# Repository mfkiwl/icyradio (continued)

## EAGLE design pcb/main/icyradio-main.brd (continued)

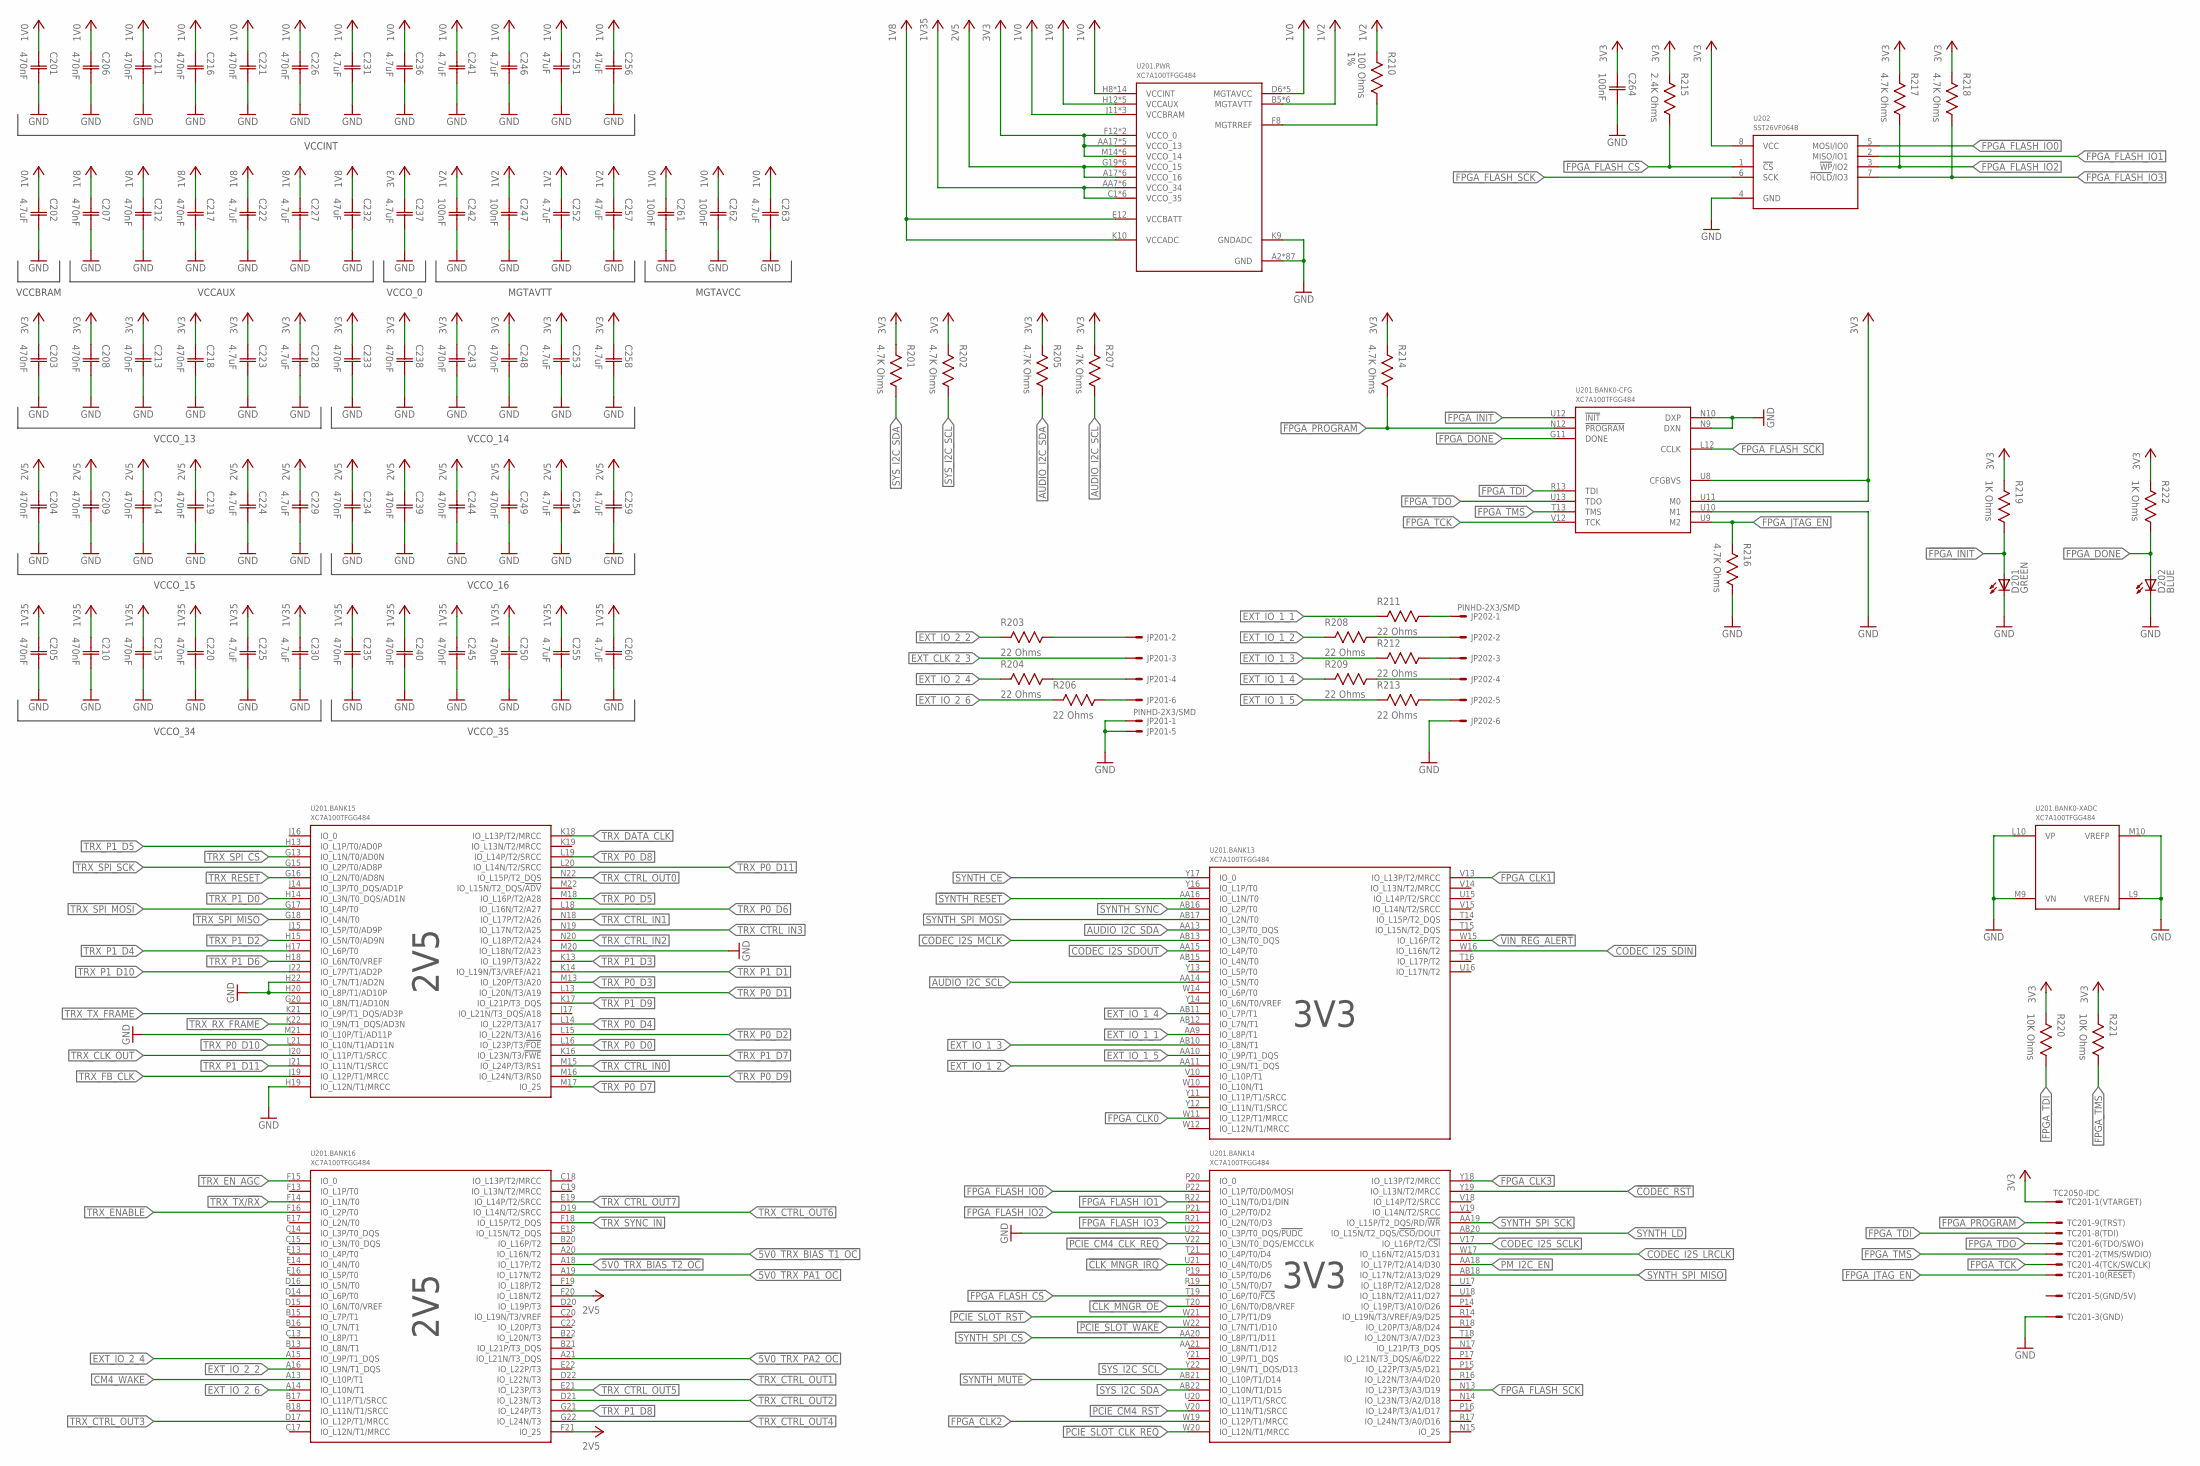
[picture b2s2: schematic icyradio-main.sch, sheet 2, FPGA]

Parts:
C201, C203, C204, C205, C206, C207, C208, C209, C210, C211, C212, C213, C214, C215, C216, C217, C218, C219, C220, C221, C226, C233, C234, C235, C238, C239, C240, C243, C244, C245, C248, C249, C250: 470nF; CAP0402
C202, C222, C223, C224, C225, C227, C228, C229, C230, C231, C236, C237, C241, C246, C252, C253, C254, C255, C258, C259, C260, C263: 4.7uF; CAP0402
C232, C251, C256, C257: 47uF; CAP0603
C242, C247, C261, C262, C264: 100nF; CAP0402
D201, D202: LED0603; 0603
JP201, JP202: PINHD-2X3/SMD; 2X03/SMD
R201, R202, R205, R207, R214, R216, R217, R218: 4.7K Ohms; RES0402
R203, R204, R206, R208, R209, R211, R212, R213: 22 Ohms; RES0402
R210: 100 Ohms; RES0402; TOLERANCE 1%
R215: 2.4K Ohms; RES0402
R219, R222: 1K Ohms; RES0402
R220, R221: 10K Ohms; RES0402
TC201: TC2050-IDC
U201: XC7A100TFGG484; FGG484
U202: SST26VF064B; WSOIC8

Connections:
1V0: C201.1 (C1), C202.1 (C1), C206.1 (C1), C211.1 (C1), C216.1 (C1), C221.1 (C1), C226.1 (C1), C231.1 (C1), C236.1 (C1), C241.1 (C1), C246.1 (C1), C251.1 (C1), C256.1 (C1), C261.1 (C1), C262.1 (C1), C263.1 (C1), U201.D6 (MGTAVCC), U201.D10 (MGTAVCC), U201.E8 (MGTAVCC), U201.F7 (MGTAVCC), U201.F9 (MGTAVCC), U201.H8 (VCCINT), U201.H10 (VCCINT), U201.J7 (VCCINT), U201.J9 (VCCINT), U201.J11 (VCCBRAM), U201.K8 (VCCINT), U201.L7 (VCCINT), U201.L11 (VCCBRAM), U201.M8 (VCCINT), U201.N7 (VCCINT), U201.N11 (VCCBRAM), U201.P8 (VCCINT), U201.P10 (VCCINT), U201.R7 (VCCINT), U201.R9 (VCCINT), U201.T8 (VCCINT), U201.T10 (VCCINT); also elsewhere on the board
1V2: C242.1 (C1), C247.1 (C1), C252.1 (C1), C257.1 (C1), R210.2, U201.B5 (MGTAVTT), U201.B7 (MGTAVTT), U201.B9 (MGTAVTT), U201.B11 (MGTAVTT), U201.C4 (MGTAVTT), U201.C8 (MGTAVTT); also elsewhere on the board
1V8: C207.1 (C1), C212.1 (C1), C217.1 (C1), C222.1 (C1), C227.1 (C1), C232.1 (C1), U201.E12 (VCCBATT), U201.H12 (VCCAUX), U201.K10 (VCCADC), U201.K12 (VCCAUX), U201.M12 (VCCAUX), U201.P12 (VCCAUX), U201.R11 (VCCAUX); also elsewhere on the board
1V35: C205.1 (C1), C210.1 (C1), C215.1 (C1), C220.1 (C1), C225.1 (C1), C230.1 (C1), C235.1 (C1), C240.1 (C1), C245.1 (C1), C250.1 (C1), C255.1 (C1), C260.1 (C1), U201.AA7 (VCCO_34), U201.AB4 (VCCO_34), U201.C1 (VCCO_35), U201.F2 (VCCO_35), U201.H6 (VCCO_35), U201.J3 (VCCO_35), U201.M4 (VCCO_35), U201.N1 (VCCO_35), U201.R5 (VCCO_34), U201.T2 (VCCO_34), U201.V6 (VCCO_34), U201.W3 (VCCO_34); also elsewhere on the board
2V5: C204.1 (C1), C209.1 (C1), C214.1 (C1), C219.1 (C1), C224.1 (C1), C229.1 (C1), C234.1 (C1), C239.1 (C1), C244.1 (C1), C249.1 (C1), C254.1 (C1), C259.1 (C1), U201.A17 (VCCO_16), U201.B14 (VCCO_16), U201.C21 (VCCO_16), U201.D18 (VCCO_16), U201.E15 (VCCO_16), U201.F20 (IO_L18N/T2), U201.F21 (IO_25), U201.F22 (VCCO_16), U201.G19 (VCCO_15), U201.H16 (VCCO_15), U201.J13 (VCCO_15), U201.K20 (VCCO_15), U201.L17 (VCCO_15), U201.N21 (VCCO_15); also elsewhere on the board
3V3: C203.1 (C1), C208.1 (C1), C213.1 (C1), C218.1 (C1), C223.1 (C1), C228.1 (C1), C233.1 (C1), C237.1 (C1), C238.1 (C1), C243.1 (C1), C248.1 (C1), C253.1 (C1), C258.1 (C1), C264.1 (C1), R201.2, R202.2, R205.2, R207.2, R214.2, R215.2, R217.2, R218.2, R219.2, R220.2, R221.2, R222.2, TC201.1, U201.AA17 (VCCO_13), U201.AB14 (VCCO_13), U201.F12 (VCCO_0), U201.M14 (VCCO_14), U201.P18 (VCCO_14), U201.R15 (VCCO_14), U201.T12 (VCCO_0), U201.T22 (VCCO_14), U201.U8 (CFGBVS), U201.U11 (M0), U201.U19 (VCCO_14), U201.V16 (VCCO_13), U201.W13 (VCCO_13), U201.Y10 (VCCO_13), U201.Y20 (VCCO_14), U202.8 (VCC); also elsewhere on the board
!5V0_TRX_BIAS_T1_OC: U201.A20 (IO_L16N/T2); also elsewhere on the board
!5V0_TRX_BIAS_T2_OC: U201.A18 (IO_L17P/T2); also elsewhere on the board
!5V0_TRX_PA1_OC: U201.A19 (IO_L17N/T2); also elsewhere on the board
!5V0_TRX_PA2_OC: U201.A21 (IO_L21N/T3_DQS); also elsewhere on the board
!CLK_MNGR_IRQ: U201.U21 (IO_L4N/T0/D5); also elsewhere on the board
!CLK_MNGR_OE: U201.T20 (IO_L6N/T0/D8/VREF); also elsewhere on the board
!CODEC_RST: U201.Y19 (IO_L13N/T2/MRCC); also elsewhere on the board
!FPGA_FLASH_CS: R215.1, U201.T19 (IO_L6P/T0/!FCS), U202.1 (!CS!)
!FPGA_INIT: D201.A, R219.1, U201.U12 (!INIT); also elsewhere on the board
!FPGA_PROGRAM: R214.1, TC201.9, U201.N12 (!PROGRAM)
!PCIE_CM4_CLK_REQ: U201.V22 (IO_L3N/T0_DQS/EMCCLK); also elsewhere on the board
!PCIE_CM4_RST: U201.V20 (IO_L11N/T1/SRCC); also elsewhere on the board
!PCIE_SLOT_CLK_REQ: U201.W20 (IO_L12N/T1/MRCC); also elsewhere on the board
!PCIE_SLOT_RST: U201.W21 (IO_L7P/T1/D9); also elsewhere on the board
!PCIE_SLOT_WAKE: U201.W22 (IO_L7N/T1/D10); also elsewhere on the board
!SYNTH_RESET: U201.AA16 (IO_L1N/T0); also elsewhere on the board
!SYNTH_SPI_CS: U201.AA20 (IO_L8P/T1/D11); also elsewhere on the board
!TRX_RESET: U201.G16 (IO_L2N/T0/AD8N); also elsewhere on the board
!TRX_SPI_CS: U201.G13 (IO_L1N/T0/AD0N); also elsewhere on the board
!VIN_REG_ALERT: U201.W15 (IO_L16P/T2); also elsewhere on the board
AUDIO_I2C_SCL: R207.1, U201.AA14 (IO_L5N/T0); also elsewhere on the board
AUDIO_I2C_SDA: R205.1, U201.AA13 (IO_L3P/T0_DQS); also elsewhere on the board
CM4_WAKE: U201.A13 (IO_L10P/T1); also elsewhere on the board
CODEC_I2S_LRCLK: U201.W17 (IO_L16N/T2/A15/D31); also elsewhere on the board
CODEC_I2S_MCLK: U201.AB13 (IO_L3N/T0_DQS); also elsewhere on the board
CODEC_I2S_SCLK: U201.V17 (IO_L16P/T2/!CSI); also elsewhere on the board
CODEC_I2S_SDIN: U201.W16 (IO_L16N/T2); also elsewhere on the board
CODEC_I2S_SDOUT: U201.AA15 (IO_L4P/T0); also elsewhere on the board
EXT_CLK_2_3: JP201.3; also elsewhere on the board
EXT_IO_1_1: R211.2, U201.AA9 (IO_L8P/T1)
EXT_IO_1_2: R208.2, U201.AA11 (IO_L9N/T1_DQS)
EXT_IO_1_3: R212.2, U201.AB10 (IO_L8N/T1)
EXT_IO_1_4: R209.2, U201.AB11 (IO_L7P/T1)
EXT_IO_1_5: R213.2, U201.AA10 (IO_L9P/T1_DQS)
EXT_IO_2_2: R203.2, U201.A16 (IO_L9N/T1_DQS)
EXT_IO_2_4: R204.2, U201.A15 (IO_L9P/T1_DQS)
EXT_IO_2_6: R206.2, U201.A14 (IO_L10N/T1)
FPGA_CLK0: U201.W11 (IO_L12P/T1/MRCC); also elsewhere on the board
FPGA_CLK1: U201.V13 (IO_L13P/T2/MRCC); also elsewhere on the board
FPGA_CLK2: U201.W19 (IO_L12P/T1/MRCC); also elsewhere on the board
FPGA_CLK3: U201.Y18 (IO_L13P/T2/MRCC); also elsewhere on the board
FPGA_DONE: D202.A, R222.1, U201.G11 (DONE)
FPGA_FLASH_IO0: U201.P22 (IO_L1P/T0/D0/MOSI), U202.5 (MOSI/IO0)
FPGA_FLASH_IO1: U201.R22 (IO_L1N/T0/D1/DIN), U202.2 (MISO/IO1)
FPGA_FLASH_IO2: R217.1, U201.P21 (IO_L2P/T0/D2), U202.3 (!WP!/IO2)
FPGA_FLASH_IO3: R218.1, U201.R21 (IO_L2N/T0/D3), U202.7 (!HOLD!/IO3)
FPGA_FLASH_SCK: U201.L12 (CCLK), U201.N13 (IO_L23P/T3/A3/D19), U202.6 (SCK)
FPGA_JTAG_EN: R216.2, TC201.10, U201.U9 (M2)
FPGA_TCK: TC201.4, U201.V12 (TCK)
FPGA_TDI: R220.1, TC201.8, U201.R13 (TDI)
FPGA_TDO: TC201.6, U201.U13 (TDO)
FPGA_TMS: R221.1, TC201.2, U201.T13 (TMS)
GND: C201.2 (C2), C202.2 (C2), C203.2 (C2), C204.2 (C2), C205.2 (C2), C206.2 (C2), C207.2 (C2), C208.2 (C2), C209.2 (C2), C210.2 (C2), C211.2 (C2), C212.2 (C2), C213.2 (C2), C214.2 (C2), C215.2 (C2), C216.2 (C2), C217.2 (C2), C218.2 (C2), C219.2 (C2), C220.2 (C2), C221.2 (C2), C222.2 (C2), C223.2 (C2), C224.2 (C2), C225.2 (C2), C226.2 (C2), C227.2 (C2), C228.2 (C2), C229.2 (C2), C230.2 (C2), C231.2 (C2), C232.2 (C2), C233.2 (C2), C234.2 (C2), C235.2 (C2), C236.2 (C2), C237.2 (C2), C238.2 (C2), C239.2 (C2), C240.2 (C2), C241.2 (C2), C242.2 (C2), C243.2 (C2), C244.2 (C2), C245.2 (C2), C246.2 (C2), C247.2 (C2), C248.2 (C2), C249.2 (C2), C250.2 (C2), C251.2 (C2), C252.2 (C2), C253.2 (C2), C254.2 (C2), C255.2 (C2), C256.2 (C2), C257.2 (C2), C258.2 (C2), C259.2 (C2), C260.2 (C2), C261.2 (C2), C262.2 (C2), C263.2 (C2), C264.2 (C2), D201.C, D202.C, JP201.1, JP201.5, JP202.6, R216.1, TC201.3, U201.A2 (GND), U201.A3 (GND), U201.A5 (GND), U201.A7 (GND), U201.A9 (GND), U201.A11 (GND), U201.A12 (GND), U201.A22 (GND), U201.AA2 (GND), U201.AA12 (GND), U201.AA22 (GND), U201.AB9 (GND), U201.AB19 (GND), U201.B3 (GND), U201.B12 (GND), U201.B19 (GND), U201.C3 (GND), U201.C6 (GND), U201.C10 (GND), U201.C12 (GND), U201.C16 (GND), U201.D3 (GND), U201.D4 (GND), U201.D8 (GND), U201.D12 (GND), U201.D13 (GND), U201.E4 (GND), U201.E5 (GND), U201.E7 (GND), U201.E9 (GND), U201.E11 (GND), U201.E20 (GND), U201.F5 (GND), U201.F11 (GND), U201.F17 (GND), U201.G5 (GND), U201.G6 (GND), U201.G7 (GND), U201.G8 (GND), U201.G9 (GND), U201.G10 (GND), U201.G12 (GND), U201.G14 (GND), U201.H1 (GND), U201.H7 (GND), U201.H9 (GND), U201.H11 (GND), U201.H19 (IO_L12N/T1/MRCC), U201.H20 (IO_L8P/T1/AD10P), U201.H21 (GND), U201.H22 (IO_L7N/T1/AD2N), U201.J8 (GND), U201.J10 (GND), U201.J12 (GND), U201.J18 (GND), U201.K5 (GND), U201.K7 (GND), U201.K9 (GNDADC), U201.K11 (GND), U201.K15 (GND), U201.L2 (GND), U201.L8 (GND), U201.L9 (VREFN), U201.L10 (VP), U201.L22 (GND), U201.M7 (GND), U201.M9 (VN), U201.M10 (VREFP), U201.M11 (GND), U201.M19 (GND), U201.M20 (IO_L18N/T2/A23), U201.M21 (IO_L10P/T1/AD11P), U201.N6 (GND), U201.N8 (GND), U201.N9 (DXN), U201.N10 (DXP), U201.N16 (GND), U201.P3 (GND), U201.P7 (GND), U201.P9 (GND), U201.P11 (GND), U201.P13 (GND), U201.R8 (GND), U201.R10 (GND), U201.R12 (GND), U201.R20 (GND), U201.T7 (GND), U201.T9 (GND), U201.T11 (GND), U201.T17 (GND), U201.U4 (GND), U201.U10 (M1), U201.U14 (GND), U201.U22 (IO_L3P/T0_DQS/!PUDC), U201.V1 (GND), U201.V11 (GND), U201.V21 (GND), U201.W8 (GND), U201.W18 (GND), U201.Y5 (GND), U201.Y15 (GND), U202.4 (GND); also elsewhere on the board
unnamed: R210.1, U201.F8 (MGTRREF)
unnamed: JP202.5, R213.1
unnamed: JP201.6, R206.1
unnamed: JP202.4, R209.1
unnamed: JP202.3, R212.1
unnamed: JP202.2, R208.1
unnamed: JP202.1, R211.1
unnamed: JP201.4, R204.1
unnamed: JP201.2, R203.1
PM_I2C_EN: U201.AA18 (IO_L17P/T2/A14/D30); also elsewhere on the board
SYNTH_CE: U201.Y17 (IO_0); also elsewhere on the board
SYNTH_LD: U201.AB20 (IO_L15N/T2_DQS/!CSO!/DOUT); also elsewhere on the board
SYNTH_MUTE: U201.AB21 (IO_L10P/T1/D14); also elsewhere on the board
SYNTH_SPI_MISO: U201.AB18 (IO_L17N/T2/A13/D29); also elsewhere on the board
SYNTH_SPI_MOSI: U201.AB17 (IO_L2N/T0); also elsewhere on the board
SYNTH_SPI_SCK: U201.AA19 (IO_L15P/T2_DQS/RD/!WR); also elsewhere on the board
SYNTH_SYNC: U201.AB16 (IO_L2P/T0); also elsewhere on the board
SYS_I2C_SCL: R202.1, U201.Y22 (IO_L9N/T1_DQS/D13); also elsewhere on the board
SYS_I2C_SDA: R201.1, U201.AB22 (IO_L10N/T1/D15); also elsewhere on the board
TRX_CLK_OUT: U201.J20 (IO_L11P/T1/SRCC); also elsewhere on the board
TRX_CTRL_IN0: U201.M15 (IO_L24P/T3/RS1); also elsewhere on the board
TRX_CTRL_IN1: U201.N18 (IO_L17P/T2/A26); also elsewhere on the board
TRX_CTRL_IN2: U201.N20 (IO_L18P/T2/A24); also elsewhere on the board
TRX_CTRL_IN3: U201.N19 (IO_L17N/T2/A25); also elsewhere on the board
TRX_CTRL_OUT0: U201.N22 (IO_L15P/T2_DQS); also elsewhere on the board
TRX_CTRL_OUT1: U201.D22 (IO_L22N/T3); also elsewhere on the board
TRX_CTRL_OUT2: U201.D21 (IO_L23N/T3); also elsewhere on the board
TRX_CTRL_OUT3: U201.D17 (IO_L12P/T1/MRCC); also elsewhere on the board
TRX_CTRL_OUT4: U201.G22 (IO_L24N/T3); also elsewhere on the board
TRX_CTRL_OUT5: U201.E21 (IO_L23P/T3); also elsewhere on the board
TRX_CTRL_OUT6: U201.D19 (IO_L14N/T2/SRCC); also elsewhere on the board
TRX_CTRL_OUT7: U201.E19 (IO_L14P/T2/SRCC); also elsewhere on the board
TRX_DATA_CLK: U201.K18 (IO_L13P/T2/MRCC); also elsewhere on the board
TRX_ENABLE: U201.F16 (IO_L2P/T0); also elsewhere on the board
TRX_EN_AGC: U201.F15 (IO_0); also elsewhere on the board
TRX_FB_CLK: U201.J19 (IO_L12P/T1/MRCC); also elsewhere on the board
TRX_P0_D0: U201.L16 (IO_L23P/T3/!FOE); also elsewhere on the board
TRX_P0_D1: U201.L13 (IO_L20N/T3/A19); also elsewhere on the board
TRX_P0_D2: U201.L15 (IO_L22N/T3/A16); also elsewhere on the board
TRX_P0_D3: U201.M13 (IO_L20P/T3/A20); also elsewhere on the board
TRX_P0_D4: U201.L14 (IO_L22P/T3/A17); also elsewhere on the board
TRX_P0_D5: U201.M18 (IO_L16P/T2/A28); also elsewhere on the board
TRX_P0_D6: U201.L18 (IO_L16N/T2/A27); also elsewhere on the board
TRX_P0_D7: U201.M17 (IO_25); also elsewhere on the board
TRX_P0_D8: U201.L19 (IO_L14P/T2/SRCC); also elsewhere on the board
TRX_P0_D9: U201.M16 (IO_L24N/T3/RS0); also elsewhere on the board
TRX_P0_D10: U201.L21 (IO_L10N/T1/AD11N); also elsewhere on the board
TRX_P0_D11: U201.L20 (IO_L14N/T2/SRCC); also elsewhere on the board
TRX_P1_D0: U201.H14 (IO_L3N/T0_DQS/AD1N); also elsewhere on the board
TRX_P1_D1: U201.K14 (IO_L19N/T3/VREF/A21); also elsewhere on the board
TRX_P1_D2: U201.H15 (IO_L5N/T0/AD9N); also elsewhere on the board
TRX_P1_D3: U201.K13 (IO_L19P/T3/A22); also elsewhere on the board
TRX_P1_D4: U201.H17 (IO_L6P/T0); also elsewhere on the board
TRX_P1_D5: U201.H13 (IO_L1P/T0/AD0P); also elsewhere on the board
TRX_P1_D6: U201.H18 (IO_L6N/T0/VREF); also elsewhere on the board
TRX_P1_D7: U201.K16 (IO_L23N/T3/!FWE); also elsewhere on the board
TRX_P1_D8: U201.G21 (IO_L24P/T3); also elsewhere on the board
TRX_P1_D9: U201.K17 (IO_L21P/T3_DQS); also elsewhere on the board
TRX_P1_D10: U201.J22 (IO_L7P/T1/AD2P); also elsewhere on the board
TRX_P1_D11: U201.J21 (IO_L11N/T1/SRCC); also elsewhere on the board
TRX_RX_FRAME: U201.K22 (IO_L9N/T1_DQS/AD3N); also elsewhere on the board
TRX_SPI_MISO: U201.G18 (IO_L4N/T0); also elsewhere on the board
TRX_SPI_MOSI: U201.G17 (IO_L4P/T0); also elsewhere on the board
TRX_SPI_SCK: U201.G15 (IO_L2P/T0/AD8P); also elsewhere on the board
TRX_SYNC_IN: U201.F18 (IO_L15P/T2_DQS); also elsewhere on the board
TRX_TX/!RX: U201.F14 (IO_L1N/T0); also elsewhere on the board
TRX_TX_FRAME: U201.K21 (IO_L9P/T1_DQS/AD3P); also elsewhere on the board

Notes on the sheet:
2V5
3V3
VCCINT
VCCBRAM
VCCAUX
VCCO_0
VCCO_13
VCCO_14
VCCO_15
VCCO_16
VCCO_34
VCCO_35
MGTAVTT
MGTAVCC

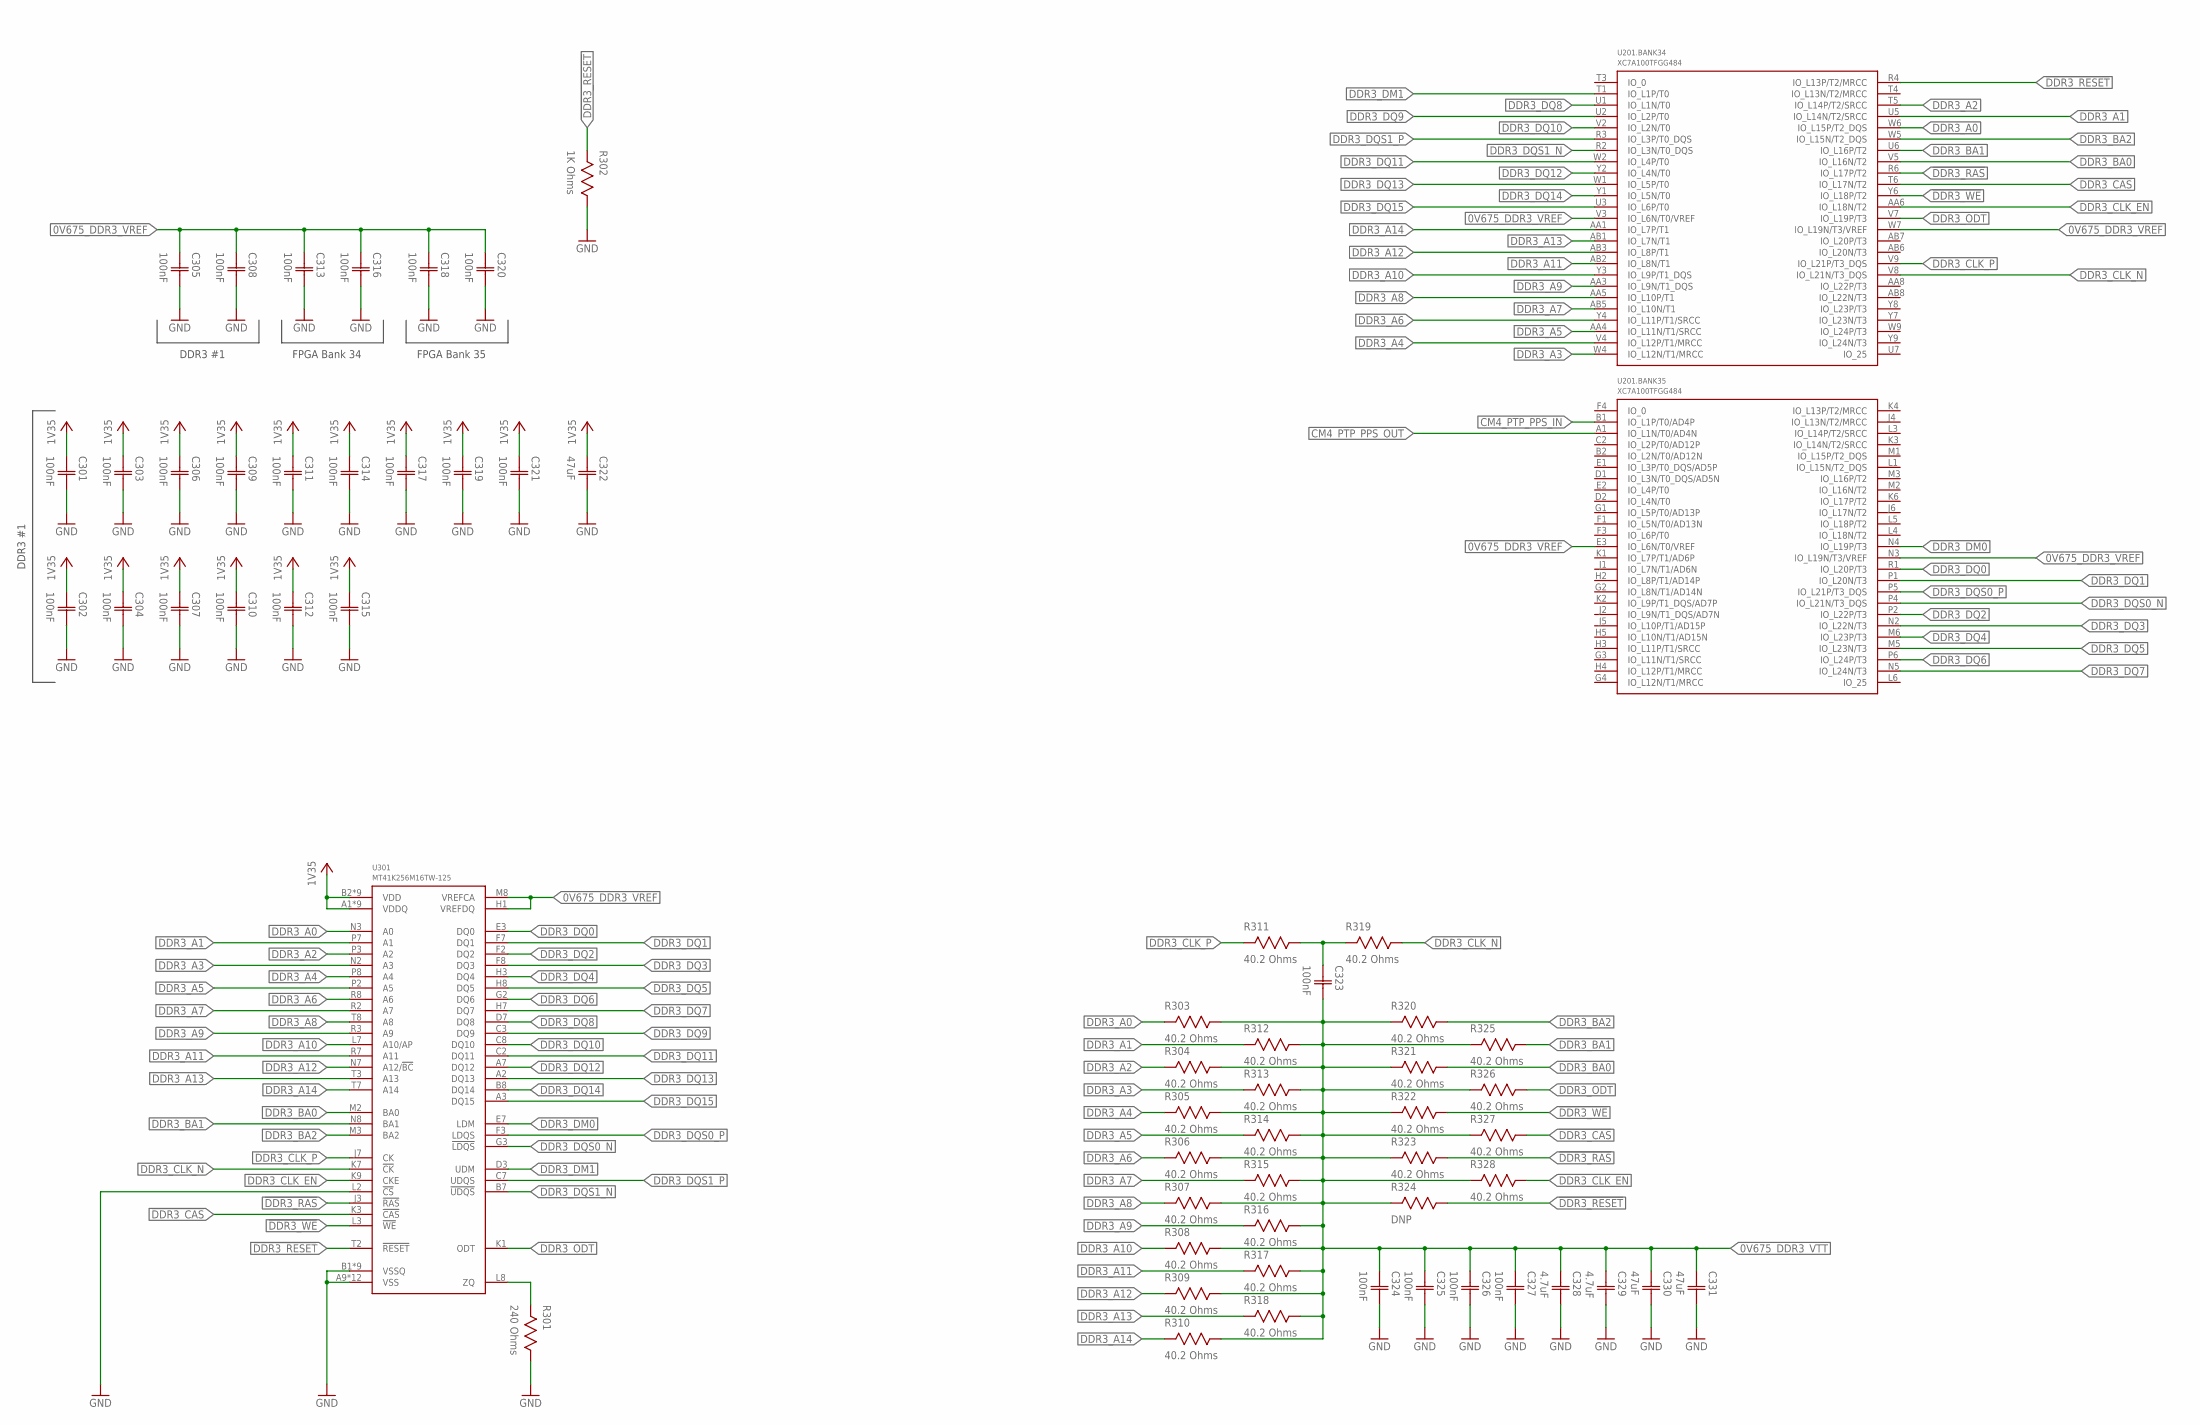
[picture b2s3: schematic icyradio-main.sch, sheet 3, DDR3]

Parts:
C301, C302, C303, C304, C305, C306, C307, C308, C309, C310, C311, C312, C313, C314, C315, C316, C317, C318, C319, C320, C321, C323, C324, C325, C326, C327: 100nF; CAP0402
C322, C330, C331: 47uF; CAP0603
C328, C329: 4.7uF; CAP0402
R301: 240 Ohms; RES0402
R302: 1K Ohms; RES0402
R303, R304, R305, R306, R307, R308, R309, R310, R311, R312, R313, R314, R315, R316, R317, R318, R319, R320, R321, R322, R323, R325, R326, R327, R328: 40.2 Ohms; RES0402
R324: DNP; RES0402
U201: XC7A100TFGG484; FGG484
U301: MT41K256M16TW-125; FBGA96_14X8

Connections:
0V675_DDR3_VREF: C305.1 (C1), C308.1 (C1), C313.1 (C1), C316.1 (C1), C318.1 (C1), C320.1 (C1), U201.E3 (IO_L6N/T0/VREF), U201.N3 (IO_L19N/T3/VREF), U201.V3 (IO_L6N/T0/VREF), U201.W7 (IO_L19N/T3/VREF), U301.H1 (VREFDQ), U301.M8 (VREFCA); also elsewhere on the board
0V675_DDR3_VTT: C323.2 (C2), C324.1 (C1), C325.1 (C1), C326.1 (C1), C327.1 (C1), C328.1 (C1), C329.1 (C1), C330.1 (C1), C331.1 (C1), R303.1, R304.1, R305.1, R306.1, R307.1, R308.1, R309.1, R310.1, R312.1, R313.1, R314.1, R315.1, R316.1, R317.1, R318.1, R320.2, R321.2, R322.2, R323.2, R324.2, R325.2, R326.2, R327.2, R328.2; also elsewhere on the board
1V35: C301.1 (C1), C302.1 (C1), C303.1 (C1), C304.1 (C1), C306.1 (C1), C307.1 (C1), C309.1 (C1), C310.1 (C1), C311.1 (C1), C312.1 (C1), C314.1 (C1), C315.1 (C1), C317.1 (C1), C319.1 (C1), C321.1 (C1), C322.1 (C1), U301.A1 (VDDQ), U301.A8 (VDDQ), U301.B2 (VDD), U301.C1 (VDDQ), U301.C9 (VDDQ), U301.D2 (VDDQ), U301.D9 (VDD), U301.E9 (VDDQ), U301.F1 (VDDQ), U301.G7 (VDD), U301.H2 (VDDQ), U301.H9 (VDDQ), U301.K2 (VDD), U301.K8 (VDD), U301.N1 (VDD), U301.N9 (VDD), U301.R1 (VDD), U301.R9 (VDD); also elsewhere on the board
!DDR3_CAS: R327.1, U201.T6 (IO_L17N/T2), U301.K3 (!CAS)
!DDR3_RAS: R323.1, U201.R6 (IO_L17P/T2), U301.J3 (!RAS)
!DDR3_RESET: R302.2, R324.1, U201.R4 (IO_L13P/T2/MRCC), U301.T2 (!RESET)
!DDR3_WE: R322.1, U201.Y6 (IO_L18P/T2), U301.L3 (!WE)
CM4_PTP_PPS_IN: U201.B1 (IO_L1P/T0/AD4P); also elsewhere on the board
CM4_PTP_PPS_OUT: U201.A1 (IO_L1N/T0/AD4N); also elsewhere on the board
DDR3_A0: R303.2, U201.W6 (IO_L15P/T2_DQS), U301.N3 (A0)
DDR3_A1: R312.2, U201.U5 (IO_L14N/T2/SRCC), U301.P7 (A1)
DDR3_A2: R304.2, U201.T5 (IO_L14P/T2/SRCC), U301.P3 (A2)
DDR3_A3: R313.2, U201.W4 (IO_L12N/T1/MRCC), U301.N2 (A3)
DDR3_A4: R305.2, U201.V4 (IO_L12P/T1/MRCC), U301.P8 (A4)
DDR3_A5: R314.2, U201.AA4 (IO_L11N/T1/SRCC), U301.P2 (A5)
DDR3_A6: R306.2, U201.Y4 (IO_L11P/T1/SRCC), U301.R8 (A6)
DDR3_A7: R315.2, U201.AB5 (IO_L10N/T1), U301.R2 (A7)
DDR3_A8: R307.2, U201.AA5 (IO_L10P/T1), U301.T8 (A8)
DDR3_A9: R316.2, U201.AA3 (IO_L9N/T1_DQS), U301.R3 (A9)
DDR3_A10: R308.2, U201.Y3 (IO_L9P/T1_DQS), U301.L7 (A10/AP)
DDR3_A11: R317.2, U201.AB2 (IO_L8N/T1), U301.R7 (A11)
DDR3_A12: R309.2, U201.AB3 (IO_L8P/T1), U301.N7 (A12/!BC)
DDR3_A13: R318.2, U201.AB1 (IO_L7N/T1), U301.T3 (A13)
DDR3_A14: R310.2, U201.AA1 (IO_L7P/T1), U301.T7 (A14)
DDR3_BA0: R321.1, U201.V5 (IO_L16N/T2), U301.M2 (BA0)
DDR3_BA1: R325.1, U201.U6 (IO_L16P/T2), U301.N8 (BA1)
DDR3_BA2: R320.1, U201.W5 (IO_L15N/T2_DQS), U301.M3 (BA2)
DDR3_CLK_EN: R328.1, U201.AA6 (IO_L18N/T2), U301.K9 (CKE)
DDR3_CLK_N: R319.1, U201.V8 (IO_L21N/T3_DQS), U301.K7 (!CK)
DDR3_CLK_P: R311.2, U201.V9 (IO_L21P/T3_DQS), U301.J7 (CK)
DDR3_DM0: U201.N4 (IO_L19P/T3), U301.E7 (LDM)
DDR3_DM1: U201.T1 (IO_L1P/T0), U301.D3 (UDM)
DDR3_DQ0: U201.R1 (IO_L20P/T3), U301.E3 (DQ0)
DDR3_DQ1: U201.P1 (IO_L20N/T3), U301.F7 (DQ1)
DDR3_DQ2: U201.P2 (IO_L22P/T3), U301.F2 (DQ2)
DDR3_DQ3: U201.N2 (IO_L22N/T3), U301.F8 (DQ3)
DDR3_DQ4: U201.M6 (IO_L23P/T3), U301.H3 (DQ4)
DDR3_DQ5: U201.M5 (IO_L23N/T3), U301.H8 (DQ5)
DDR3_DQ6: U201.P6 (IO_L24P/T3), U301.G2 (DQ6)
DDR3_DQ7: U201.N5 (IO_L24N/T3), U301.H7 (DQ7)
DDR3_DQ8: U201.U1 (IO_L1N/T0), U301.D7 (DQ8)
DDR3_DQ9: U201.U2 (IO_L2P/T0), U301.C3 (DQ9)
DDR3_DQ10: U201.V2 (IO_L2N/T0), U301.C8 (DQ10)
DDR3_DQ11: U201.W2 (IO_L4P/T0), U301.C2 (DQ11)
DDR3_DQ12: U201.Y2 (IO_L4N/T0), U301.A7 (DQ12)
DDR3_DQ13: U201.W1 (IO_L5P/T0), U301.A2 (DQ13)
DDR3_DQ14: U201.Y1 (IO_L5N/T0), U301.B8 (DQ14)
DDR3_DQ15: U201.U3 (IO_L6P/T0), U301.A3 (DQ15)
DDR3_DQS0_N: U201.P4 (IO_L21N/T3_DQS), U301.G3 (!LDQS)
DDR3_DQS0_P: U201.P5 (IO_L21P/T3_DQS), U301.F3 (LDQS)
DDR3_DQS1_N: U201.R2 (IO_L3N/T0_DQS), U301.B7 (!UDQS)
DDR3_DQS1_P: U201.R3 (IO_L3P/T0_DQS), U301.C7 (UDQS)
DDR3_ODT: R326.1, U201.V7 (IO_L19P/T3), U301.K1 (ODT)
GND: C301.2 (C2), C302.2 (C2), C303.2 (C2), C304.2 (C2), C305.2 (C2), C306.2 (C2), C307.2 (C2), C308.2 (C2), C309.2 (C2), C310.2 (C2), C311.2 (C2), C312.2 (C2), C313.2 (C2), C314.2 (C2), C315.2 (C2), C316.2 (C2), C317.2 (C2), C318.2 (C2), C319.2 (C2), C320.2 (C2), C321.2 (C2), C322.2 (C2), C324.2 (C2), C325.2 (C2), C326.2 (C2), C327.2 (C2), C328.2 (C2), C329.2 (C2), C330.2 (C2), C331.2 (C2), R301.1, R302.1, U301.A9 (VSS), U301.B1 (VSSQ), U301.B3 (VSS), U301.B9 (VSSQ), U301.D1 (VSSQ), U301.D8 (VSSQ), U301.E1 (VSS), U301.E2 (VSSQ), U301.E8 (VSSQ), U301.F9 (VSSQ), U301.G1 (VSSQ), U301.G8 (VSS), U301.G9 (VSSQ), U301.J2 (VSS), U301.J8 (VSS), U301.L2 (!CS), U301.M1 (VSS), U301.M9 (VSS), U301.P1 (VSS), U301.P9 (VSS), U301.T1 (VSS), U301.T9 (VSS); also elsewhere on the board
unnamed: R301.2, U301.L8 (ZQ)
unnamed: C323.1 (C1), R311.1, R319.2

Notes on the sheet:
DDR3 #1
FPGA Bank 34
FPGA Bank 35
